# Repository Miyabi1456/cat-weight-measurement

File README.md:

# cat-weight-measurement

猫のトイレにロードセルを取り付けて、体重、トイレ時間、頻度などを計測するためのプログラムとハードウェアです。
ウェブアプリで計測結果を可視化できるようになっています。

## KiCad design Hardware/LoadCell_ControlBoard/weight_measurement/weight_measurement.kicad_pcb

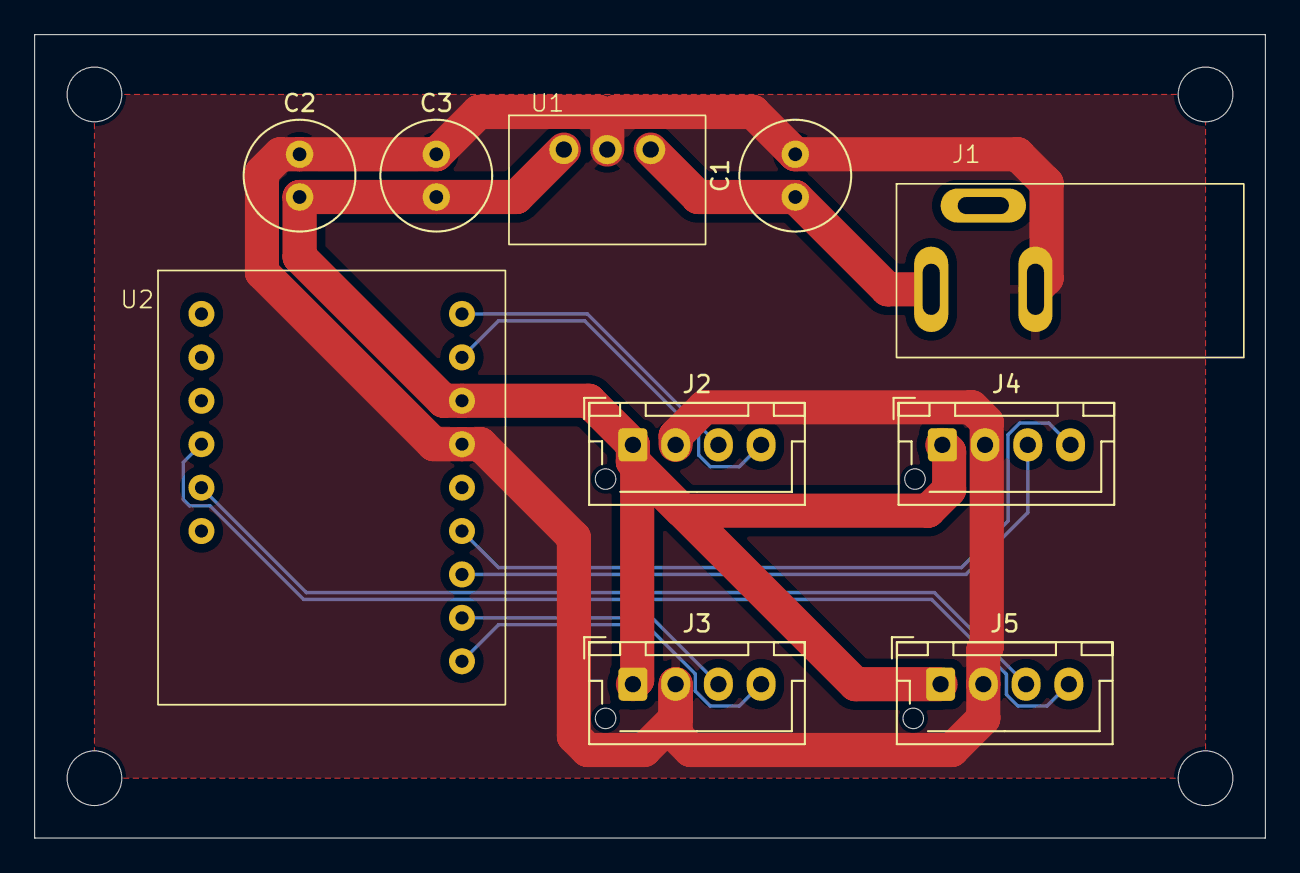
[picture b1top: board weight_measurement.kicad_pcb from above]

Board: 2 copper layers, 72.0 x 47.0 mm, 10 parts (0 on the bottom side), 11 nets.

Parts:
C1, C2: C_Polarized; C_Radial_D6.3mm_H5.0mm_P2.50mm
C3: C; C_Radial_D6.3mm_H5.0mm_P2.50mm
J1: Jack-DC; DC_jack
J2, J3, J4, J5: Conn_01x04_Pin; JST_XH_B4B-XH-AM_1x04_P2.50mm_Vertical
U1: M78AR
U2: M5StampS3

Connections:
GND: C1.2, C2.2, C3.2, J1.3, J2.2, J3.2, J4.2, J5.2, U1.2 (GND), U2.12 (GND)
unnamed: C2.1, C3.1, J2.1, J3.1, J4.1, J5.1, U1.3 (Vout), U2.13 (5V)
unnamed: J2.3, U2.15 (IO15)
unnamed: J2.4, U2.14 (IO13)
unnamed: J3.3, U2.8 (IO3)
unnamed: J3.4, U2.7 (IO1)
unnamed: J4.3, U2.9 (IO5)
unnamed: J4.4, U2.10 (IO7)
unnamed: J5.3, U2.5 (IO43)
unnamed: J5.4, U2.4 (IO44)
unnamed: C1.1, J1.2, U1.1 (Vin)
